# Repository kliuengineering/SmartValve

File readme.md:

# Smart Valve Shield for FRDM-K66F
- Authours
    - Amir
    - Kevin
    - Toan

## Preliminary Product Rendering

## Peripherals On the Shield
**Note: refer to the detailed BOM for specific components.**
1. USB-C power input
2. ESP32S module (38 pins)
3. Class AB amplifier
4. RGB LED module
5. Pressure sensor Qwiic adapter
6. Header pins for servo motor
7. Various pin sockets
8. Various passive components

## Hardware
The design is simple - we want to maximize the real estate of the shield so it becomes a sandbox tool for education purposes. The project about SmartValve is just a simple example of showing you its use case for education. To be fair - K66F is a development platform and is naive for commercial implementations.

### Circuits

### Routing

## Software

### Installations
1. If you are using Windows, then your machine may require an USB driver for the ESP32 MCU. You can download it here [USB Driver for Windows](Tools/CP210x_Universal_Windows_Driver.zip)

2. Follow the [ESP32 Markdown Documentation](./ESPServer/espserver.md) for server-side details.

### Data Logging Interface

## Future Work
1. Exploring radio-frequency applications.
2. Implementing TinyML on ESP to carry out more mature edge computing.

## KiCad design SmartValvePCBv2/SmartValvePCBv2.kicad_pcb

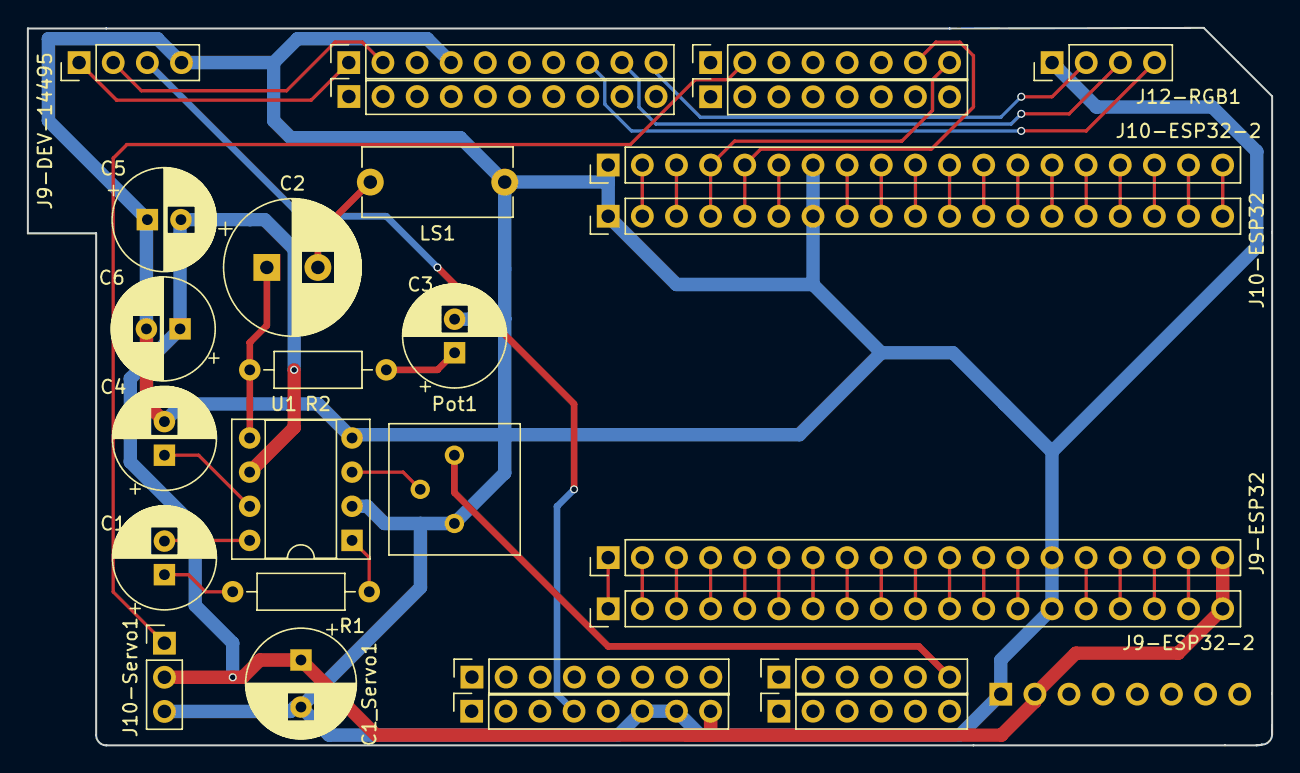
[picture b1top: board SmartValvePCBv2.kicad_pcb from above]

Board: 2 copper layers, 92.6 x 53.4 mm, 28 parts (1 on the bottom side), 52 nets.

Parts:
C1, C4: 10uF; CP_Radial_D7.5mm_P2.50mm
C1_Servo1: C_Polarized_US; CP_Radial_D8.0mm_P3.50mm
C2: 470uF; CP_Radial_D10.0mm_P3.80mm
C3: 0.05uF; CP_Radial_D7.5mm_P2.50mm
C5: 0.1uF; CP_Radial_D7.5mm_P2.50mm
C6: 100uF; CP_Radial_D7.5mm_P2.50mm
J1, J5: Power; PinSocket_1x08_P2.54mm_Vertical
J2, J6: Digital/PWM; PinSocket_1x10_P2.54mm_Vertical
J3, J7: Analog; PinSocket_1x06_P2.54mm_Vertical
J4, J8: Digital/PWM; PinSocket_1x08_P2.54mm_Vertical
J9-DEV-14495, J12-RGB1: Conn_01x04; PinHeader_1x04_P2.54mm_Vertical
J9-ESP32, J9-ESP32-2, J10-ESP32, J10-ESP32-2: Conn_01x19; PinHeader_1x19_P2.54mm_Vertical
J10-Servo1: Conn_01x03; PinHeader_1x03_P2.54mm_Vertical
J11-USBC1: Conn_01x08; PinHeader_1x08_P2.54mm_Horizontal
LS1: Speaker; C_Disc_D11.0mm_W5.0mm_P10.00mm
Pot1: 10k; Potentiometer_Bourns_3386P_Vertical
R1: 1.2k; R_Axial_DIN0207_L6.3mm_D2.5mm_P10.16mm_Horizontal
R2: 10; R_Axial_DIN0207_L6.3mm_D2.5mm_P10.16mm_Horizontal
U1: LM386; DIP-8_W7.62mm_Socket

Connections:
+3V3: J1.4, J9-DEV-14495.3
Audio1: J7.6, Pot1.1
GND: C1_Servo1.2, C3.2, C4.2, C5.1, C6.2, J1.6, J1.7, J2.4, J9-DEV-14495.4, J9-ESP32.14, J9-ESP32-2.14, J10-ESP32.1, J10-ESP32.7, J10-ESP32-2.1, J10-ESP32-2.7, J10-Servo1.3, J11-USBC1.1, J12-RGB1.1, LS1.2, Pot1.3, U1.2 (-), U1.4 (GND)
unnamed: C1.1, R1.1
unnamed: C1.2, U1.8 (GAIN)
unnamed: C2.1, R2.1, U1.5
unnamed: C2.2, LS1.1
unnamed: C3.1, R2.2
unnamed: J9-ESP32.1, J9-ESP32-2.1
unnamed: J9-ESP32.2, J9-ESP32-2.2
unnamed: J9-ESP32.3, J9-ESP32-2.3
unnamed: J9-ESP32.4, J9-ESP32-2.4
unnamed: J9-ESP32.5, J9-ESP32-2.5
unnamed: J9-ESP32.6, J9-ESP32-2.6
unnamed: J9-ESP32.7, J9-ESP32-2.7
unnamed: J9-ESP32.8, J9-ESP32-2.8
unnamed: J9-ESP32.9, J9-ESP32-2.9
unnamed: J9-ESP32.10, J9-ESP32-2.10
unnamed: J9-ESP32.11, J9-ESP32-2.11
unnamed: J9-ESP32.12, J9-ESP32-2.12
unnamed: J9-ESP32.13, J9-ESP32-2.13
unnamed: J9-ESP32.15, J9-ESP32-2.15
unnamed: J9-ESP32.16, J9-ESP32-2.16
unnamed: J9-ESP32.17, J9-ESP32-2.17
unnamed: J9-ESP32.18, J9-ESP32-2.18
unnamed: J10-ESP32.2, J10-ESP32-2.2
unnamed: J10-ESP32.3, J10-ESP32-2.3
unnamed: J10-ESP32.6, J10-ESP32-2.6
unnamed: J10-ESP32.8, J10-ESP32-2.8
unnamed: J10-ESP32.9, J10-ESP32-2.9
unnamed: J10-ESP32.10, J10-ESP32-2.10
unnamed: J10-ESP32.11, J10-ESP32-2.11
unnamed: J10-ESP32.12, J10-ESP32-2.12
unnamed: J10-ESP32.13, J10-ESP32-2.13
unnamed: J10-ESP32.14, J10-ESP32-2.14
unnamed: J10-ESP32.15, J10-ESP32-2.15
unnamed: J10-ESP32.16, J10-ESP32-2.16
unnamed: J10-ESP32.17, J10-ESP32-2.17
unnamed: J10-ESP32.18, J10-ESP32-2.18
unnamed: J10-ESP32.19, J10-ESP32-2.19
unnamed: R1.2, U1.1 (GAIN)
unnamed: Pot1.2, U1.3 (+)
unnamed: C4.1, U1.7 (BYPASS)
PTC2: J4.2, J10-Servo1.1
UA0: J4.8, J10-ESP32.4, J10-ESP32-2.4
UA1: J4.7, J10-ESP32.5, J10-ESP32-2.5
VCC: C1_Servo1.1, C5.2, C6.1, J1.8, J9-ESP32.19, J9-ESP32-2.19, J10-Servo1.2, J11-USBC1.2, U1.6 (V+)
blue: J2.8, J12-RGB1.4
green: J2.9, J12-RGB1.3
red: J2.10, J12-RGB1.2
scl_p: J2.1, J9-DEV-14495.1
sda_p: J2.2, J9-DEV-14495.2

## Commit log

2025-02-09 project kicked-off
2025-03-06 added sample code for k66f and esp32 server
2025-03-06 added espserver.md and pictures
2025-03-06 fixed the picture urls and added something to espserver.md
2025-03-19 New landing page for HTTP server
2025-04-06 added usb driver tool.
2025-04-08 added hardware folder; added md documentation.
2025-04-08 new code for espserver.ino and main.cpp
2025-04-09 Added AI
2025-04-09 Fixed bugs in K66 code
